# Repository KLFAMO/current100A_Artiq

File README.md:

# current100A_Artiq
100A current driver compatible with Artiq. At the moment, device is compatible with Sinara package size and includes all Sinara connectors. There is no software compatibility yet.

## High power circuit

Power supply - two wires (+ and -) from Delta Power Supply. (will be WAGO connector asap).
Warning: 

Coil 1 (L1) - two wires from one coil (will be WAGO connector asap)

Coil 2 (L2) - two wires from second coil (this coil is direction switchable) (will be WAGO connector asap)

LEM IN 100-S is used for current measurement.

## Control board

Power supply MSTBA green connector (0 and +12V) for control board.

Ethernet - User Interface communication.

SMA input - (-10V to +10V) current control by voltage (from external control program). 1V -> 10A

4x BNC inputs - not used yet

USB micro - not used yet

# User Interface

User interface is available via TCP/IP on port 10. Depending on configuration IP address is static or taken from DHCP - this must be set when programming uC. After connecting to the device user is able to change setting by sending commands.

## Commands
### Bbasic control

`MODE 0` - switch off current

`MODE 1` - current control via voltage input (SMA input on front panel)

`MODE 2` - current control via ethernet user interface (`CUR` command)

`CUR 10.2` - set current 10.2 A (only in mode 2)

`IMAX 25` - set max possible current value to 25A

`ERMAX 1` - max 1A change in each cycle (0.1ms)

### Advanced settings

`MODE 3` - set gate voltage using `VG` parameter

`I -0.04` - set gain -0.04 (this is bese gain for 50A - it is rescaled by uC for lower current due to udjust transistor characteristics)

`DIR x` - L2 coil current direction (x=-1: current positive, x=1: current negative, x=0: no current - all transistors blocked)

`DST x` - direction switching treshold; current direction switchin in coil L2 is possible only if absolute current value is less than x

`VG` - current gate voltage; in `MODE 3` is set manually

`CALIB 1` - gate voltage - current characteristics callibration. Improves current control.

`CALIB 4` - LEM zero current callibration (automaticaly done during startup)

## License

[MIT](https://opensource.org/licenses/MIT)

# Acknowledgments
This work has received funding from the European Partnership on Metrology, co-financed by the European Union’s Horizon Europe Research and Innovation Programme and by the Participating States, under grant number 22IEM01 TOCK.

# Issues

Please add your comments in `Issues` Github section (in top of this website).

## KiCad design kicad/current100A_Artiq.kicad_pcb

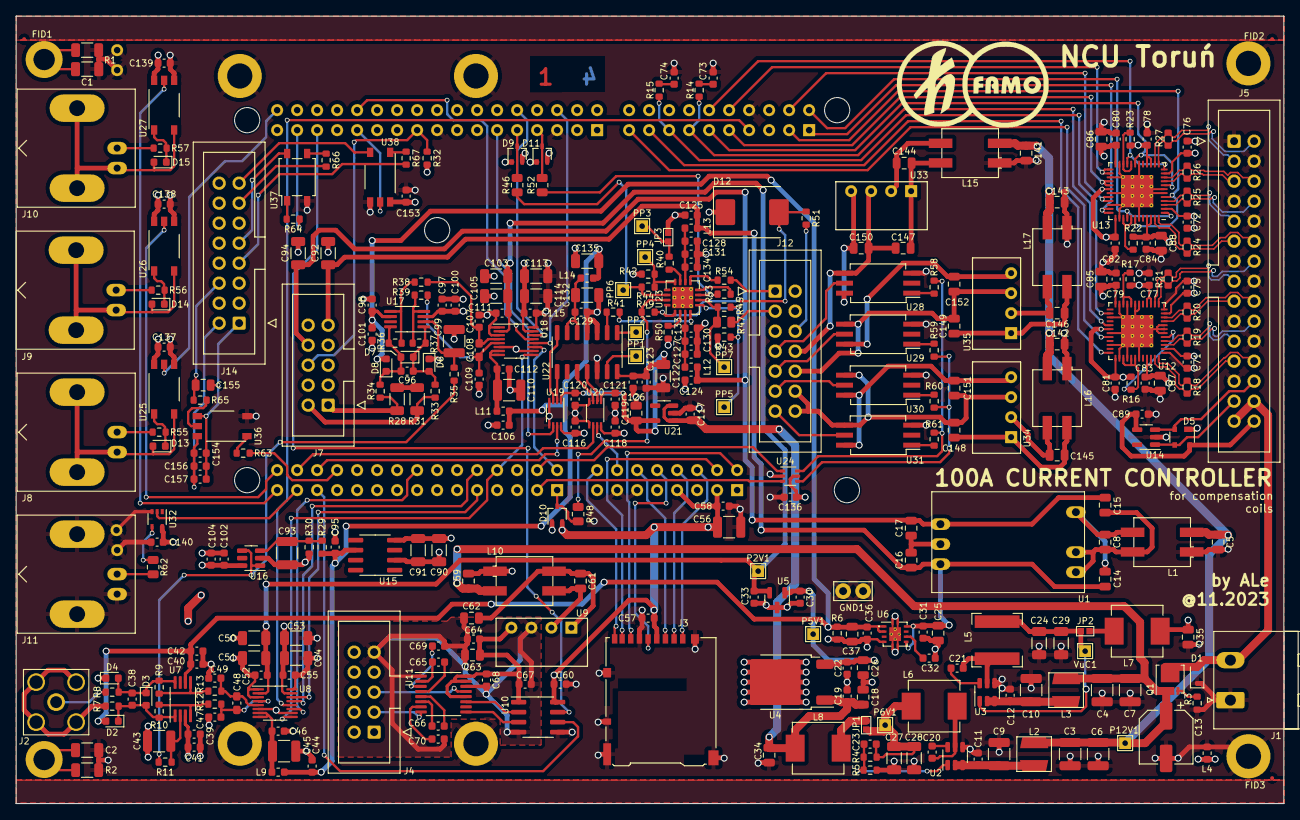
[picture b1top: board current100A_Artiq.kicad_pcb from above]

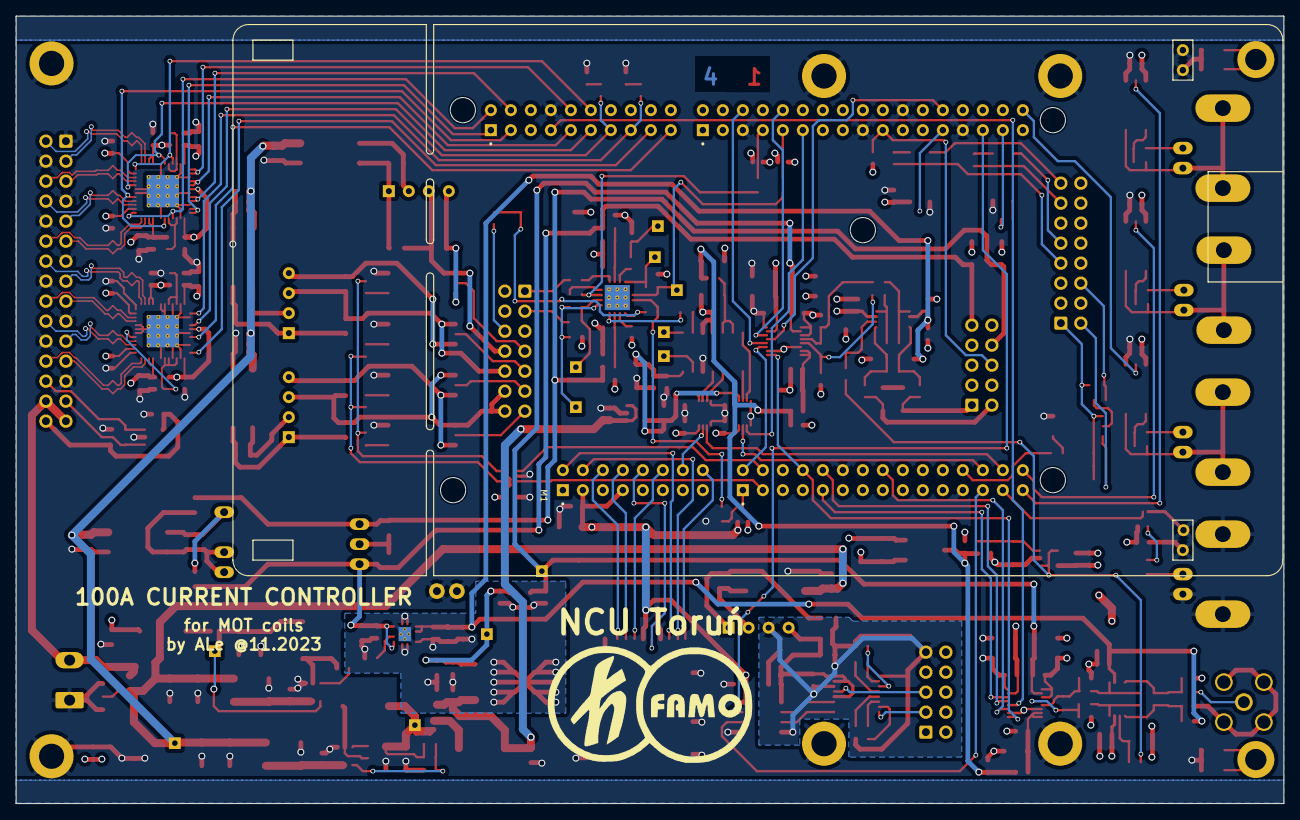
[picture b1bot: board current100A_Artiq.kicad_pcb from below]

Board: 4 copper layers, 161.0 x 100.0 mm, 337 parts (2 on the bottom side), 210 nets.

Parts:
C1, C2: GCJ31BR73A102KXJ1L; C_1206_3216Metric
C3, C4, C6, C7, C56: 10u X7R 50V; C_1210_3225Metric
C5, C8, C16, C17, C18, C25, C26, C37, C59, C61, C63, C141, C142, C143, C144, C145, C146, C150, C151, C152: GRM21BR61E106KA73L; C_0805_2012Metric
C9, C10: GCM32ER71E106KA57K; C_1210_3225Metric
C11, C12, C19, C20, C21, C22, C30, C31, C33, C36, C57, C58, C60, C64, C65, C67, C68, C71, C72, C75, C76, C77, C78, C79, C80, C81, C82, C83, C84, C89, C116, C118, C120, C121, C130, C131, C136, C137, C138, C139, C140, C153, C156: 100n 50V X7R; C_0603_1608Metric
C13: UCW1E470MCL1GS; CP_Elec_6.3x7.7
C14, C15, C62, C147, C148, C149: 1n C0G 100V; C_0805_2012Metric
C23, C39, C40, C46, C52, C55, C97, C98, C102, C111, C112, C126, C129, C133, C134, C154: 100p 50V C0G; C_0603_1608Metric
C24, C27, C28, C29: GRM31CR71A226KE15L; C_1206_3216Metric
C32: GRM1885C1H103JA01D; C_0603_1608Metric
C34, C35, C85, C86, C87, C88: GRM21BR71A106KA73L; C_0805_2012Metric
C38, C47, C49, C96, C107, C109: 1n 50V C0G; C_0603_1608Metric
C41, C42, C44, C95, C100, C101, C104, C106, C117, C124, C125, C127, C128, C157: GCM188R71E105KA64J; C_0603_1608Metric
C43, C93, C99: C1210C334J3JACAUTO; C_1210_3225Metric
C45, C110: 47UF 10V X7R; C_1210_3225Metric
C48, C108: 470p 50V C0G; C_0603_1608Metric_Pad1.08x0.95mm_HandSolder
C50, C53, C90, C92, C94, C103, C113, C122: GCM31CR71C106KA64L; C_1206_3216Metric
C51, C54, C91, C105, C114, C132, C135: GRM31C5C1H104JA01L; C_1206_3216Metric
C66, C69, C70: GCM188R71E474KA64D; C_0603_1608Metric
C73, C74: 82p 50V C0G; C_0603_1608Metric
C115: 100p C0G 50V; C_0603_1608Metric
C119: GCM21BR71C335KA73L; C_0805_2012Metric
C123: GRM31C5C1H104JA01L; C_0603_1608Metric
C155: 22n C0G 25V; C_0805_2012Metric
D1: SD12C-01FTG; D_SOD-323
D2, D4, D6, D8: TSS40U-RGG; D_0603_1608Metric
D3, D7: CZRU52C4V3; D_0603_1608Metric
D5: WE 8240136; SOT-143
D9, D10, D11: BAT54SW; SOT-323_SC-70
D12: 5.0SMDJ12AS; D_SMC
D13, D14, D15: TS4148C RZG; D_0603_1608Metric
FID1, FID2, FID3: Fiducial; Fiducial_0.5mm_Mask1.5mm
G1: KL_FAMO_LOGO; kl_famo_logo
G2: KL_FAMO_LOGO; kl_famo_logo_small
GND1: PAD; TestPoint_Bridge_Pitch2.54mm_Drill1.0mm
H1, H2: MountingHole_Pad; MountingHole_2.7mm_M2.5_DIN965_Pad
H3, H4, H5, H6, H7, H8: MountingHole_Pad; MountingHole_3.2mm_M3_DIN965_Pad
J1: MSTBA2.5/2-G-5.08 1757242; PhoenixContact_MSTBA_2,5_2-G-5,08_1x02_P5.08mm_Horizontal
J2: RF2-49B-T-00-50-G-HDW; SMA_Amphenol_132203-12_Horizontal
J3: DM3AT-SF-PEJM5; microSD_HC_Hirose_DM3AT-SF-PEJM5
J4, J7: N2510-6002-RB; IDC-Header_2x05_P2.54mm_Vertical
J5: N2530-6002-RB; IDC-Header_2x15_P2.54mm_Vertical
J8: B6252H5-NPP3G-50; BNC_Amphenol_B6252HB-NPP3G-50_Horizontal
J9, J10, J11: 5227161-1; BNC_Amphenol_B6252HB-NPP3G-50_Horizontal
J12: N2514-6002RB; IDC-Header_2x07_P2.54mm_Vertical
J14: N2516-6002-RB; IDC-Header_2x08_P2.54mm_Vertical
JP1, JP2: Jumper_NO_Small; GS2_small
JP3: Jumper_2_Bridged; GS2_small
L1, L10, L15, L16, L17: 50225C Murata; L_CommonMode_Murata_5000
L2, L3: LQH44PH220MPRL; L_MURATA_LQH44
L4: BLM18KG331SN1D; L_0603_1608Metric
L5: SRN6045-3R3Y; L_Bourns-SRN6028
L6: IHLP2525CZER100M01; L_Vishay_IHLP-2525
L7, L8: IHLP2525CZER220M11; L_Vishay_IHLP-2525
L9, L11, L12, L13, L14: BLM18HE102SN1D; L_0603_1608Metric
M1: NUCLEO-H743ZI; MODULE_NUCLEO-F746ZG_mini_M
P2V1, P5V1, P6V1, P12V1: TestPoint; TestPoint_THTPad_1.5x1.5mm_Drill0.7mm
PP1, PP2, PP3, PP4, PP5, PP6, PP7: PAD; TestPoint_THTPad_1.5x1.5mm_Drill0.7mm
Q1: SISS27DN-T1-GE3; Diodes_PowerDI3333-8
R1, R2: HV732BTTD1004F; R_1206_3216Metric
R3, R6, R44, R51, R65: 10k 1%; R_0603_1608Metric
R4, R5: 196k 1%; R_0603_1608Metric
R7, R8, R33, R34: 4,99k 1%; R_0603_1608Metric
R9, R10, R36, R37: 2k 1%; R_0603_1608Metric
R11, R32, R35, R40, R41, R43, R45, R49, R53, R54, R55, R56, R57, R63, R64, R67: 1k 1%; R_0603_1608Metric
R12, R13, R38, R39: 49,9R 1%; R_0603_1608Metric
R14, R15: 220R 1%; R_0603_1608Metric
R16, R17, R18, R19, R20, R21, R22, R23, R24, R25, R26, R27: 100R 1%; R_0603_1608Metric
R28, R31: RQ73C2B20RBTD; R_1206_3216Metric
R29, R30: 10k 0,1% 10ppm; R_0603_1608Metric
R42: DNP; R_0603_1608Metric
R46, R47, R48, R52: 100R 1%; R_0805_2012Metric
R50: 910R 1%; R_0603_1608Metric
R58, R59, R60, R61: 150R 1%; R_0603_1608Metric
R62: 100R; R_0805_2012Metric
R66: 2k4 1%; R_0603_1608Metric
U1: TME1215S; TDK_DCDC_CCG6_10
U2: AP63200WU-7; TSOT-23-6
U3: AP63203WU-7; TSOT-23-6
U4: LD29150DT50R; TO-252-2
U5: AP7313-25SAG-7; SOT-23
U6: TPS7A3001DRBx; Texas_VSON-8_1EP_3x3mm_P0,65mm_vias
U7, U17: THS4561IDGKx; MSOP-8_3x3mm_P0.65mm
U8, U18: LTC2380CMS-24#PBF; MSOP-16_3x4mm_P0.5mm
U9: AM1SS-1203SJZ; AM1SS-xxxxS
U10: ADuM121N; SOIC-8_3.9x4.9mm_P1.27mm
U11: MAX3221ExPWR; TSSOP-16_4.4x5mm_P0.65mm
U12, U13: SN65MLVD040RGZT; VQFN-48-1EP_7x7mm_P0.5mm_EP4.1x4.1mm_ThermalVias
U14: 24AA02E48T-I/OT; SOT-23-5
U15: ADR4540BRZ; SOIC-8_3.9x4.9mm_P1.27mm
U16: ADA4895-1ARJZ; SOT-23-6
U19, U20: 74LVC2T45DC,125; VSSOP-8_2.3x2mm_P0.5mm
U21: LP2981-50DBVR; SOT-23-5
U22: MAX5719AGSD+; SOIC-14_3.9x8.7mm_P1.27mm
U23: OPA4191xRUMx; WQFN-16-1EP_4x4mm_P0.65mm_EP2.7x2.7mm_ThermalVias
U24: NC7WZ17P6X; SOT-363_SC-70-6
U25, U26, U27, U36, U38: TLP2361(TPL,E; MFSOP6-5_4.4x3.6mm_P1.27mm
U28, U29, U30, U31: TLP701AF(F); SSO-6_6.8x4.6mm_P1.27mm_Clearance7mm
U32: NL17SZ16DFT2G; SOT-353_SC-70-5
U33, U34, U35: TME1215S; AM1SS-xxxxS
U37: TLP175A; SO-4_4.4x4.3mm_P2.54mm
VuC1: TestPoint; TestPoint_THTPad_1.5x1.5mm_Drill0.7mm

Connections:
+2V5: C33.2, C50.1, C51.2, C52.1, C103.1, C105.2, C111.1, P2V1.1, U5.2 (VO), U8.2 (VDD), U18.2 (VDD)
+3V3: C35.1, C53.1, C54.2, C55.1, C56.1, C57.1, C58.1, C60.2, C71.1, C72.1, C75.1, C76.1, C77.1, C78.1, C79.1, C80.1, C81.1, C82.1, C83.1, C84.1, C85.1, C86.1, C87.1, C88.1, C113.1, C114.2, C115.1, C116.2, C118.2, C136.1, C137.1, C138.1, C139.1, C140.1, C153.1, D9.2 (K), D10.2 (K), D11.2 (K), J3.4 (VDD), L7.1, M1.CN8_3 (IOREF_CN8), M1.CN8_7 (+3V3_CN8), R16.2, R17.2, R22.2, R23.2, R32.1, U8.15 (OVDD), U10.8 (VDD2), U12.2 (VCC), U12.11 (VCC), U12.15 (VCC), U12.16 (VCC), U12.24 (VCC), U12.30 (PDN), U12.37 (VCC), U12.45 (VCC), U12.46 (VCC), U13.2 (VCC), U13.11 (VCC), U13.15 (VCC), U13.16 (VCC), U13.24 (VCC), U13.30 (PDN), U13.37 (VCC), U13.45 (VCC), U13.46 (VCC), U18.15 (OVDD), U19.8 (VCCB), U20.8 (VCCB), U24.5 (V+), U25.6 (VCC), U26.6 (VCC), U27.6 (VCC), U32.5 (V+), U38.6 (VCC)
+4V: C44.1, C95.1, C106.1, C135.1, L9.1, L11.1, L14.1, R29.1, U15.6 (VOUT)
+5VA: C22.2, C26.1, C30.2, C39.1, C41.1, C90.1, C91.2, C97.1, C100.1, C102.1, C104.1, D4.1 (K), D6.1 (K), P5V1.1, U4.3 (OUT), U5.1 (VI), U7.3 (V+), U15.2 (VIN), U16.6 (V+), U17.3 (V+)
+5VD: C119.1, C120.2, C121.2, C122.1, C123.2, C126.1, U19.1 (VCCA), U20.1 (VCCA), U21.5 (VOUT), U22.14 (VDD)
+6V: C18.1, C19.2, C34.1, C117.1, L8.1, U4.1 (INP), U21.1 (VIN), U21.3 (ON/~OFF)
+12V: C3.1, C4.1, C5.1, C6.1, C7.1, C13.1, C59.1, C141.1, C142.1, C143.1, L1.2, L2.2, L3.2, L10.2, L15.2, L16.2, L17.2, P12V1.1, Q1.1 (S), Q1.2 (S), Q1.3 (S)
+15V: C15.1, C17.2, C94.1, C124.1, J7.8, L12.2, U1.4 (+VOUT)
-15V: C14.1, C16.1, C25.1, C31.1, C92.1, C125.1, J7.9, L13.2, U1.6 (-VOUT), U6.5 (EN), U6.8 (IN)
-VSW: C36.1, C37.1, C40.2, C42.2, C98.2, C101.2, D2.2 (A), D8.2 (A), R6.1, U6.1 (OUT), U6.2 (FB), U7.6 (V-), U17.6 (V-)
/15A_ON: M1.CN9_30 (D64/PG1/IO), U26.5 (VO)
/100A_ON: M1.CN9_29 (D65/PG0/IO), U27.5 (VO)
/ADC_CNV: M1.CN9_8 (D54/PD4/USART_B_RTS), U8.9 (CNV), U18.9 (CNV)
/AUX_SPAN: D9.3 (COM), M1.CN10_9 (A7/PF5/ADC3_IN4), R46.2
/Analog input1/ADC1INM: R9.2, R13.2, U7.5 (-)
/Analog input1/ADC1INP: R10.2, R12.2, U7.4 (+)
/Analog input1/IN_gnd: J2.2 (Ext), R7.1
/Analog input1/VREFB: C45.1, C46.1, L9.2, U8.7 (REF), U8.8 (REF/*DGC)
/Analog input1/VREF_P: R11.2, R35.2, U16.1, U16.4 (-)
/COIL_SPAN: D10.3 (COM), M1.CN9_1 (A0/PA3/ADC123_IN3), R48.2
/DEL_CC: M1.CN10_25 (D31/PE2/QSPI_BK1_IO2), U38.5 (VO)
/DEL_PWM: M1.CN9_24 (D61/PF8/SAI_B_SCK), R63.2
/DEL_RSD: M1.CN10_31 (XD33/PB0/TIMER_D_PWM1), R64.2
/DIR_L2: M1.CN10_34 (D35/PB11/TIMER_C_PWM3), U25.5 (VO)
/Digital inputs/output1/12V_pom4: C144.1, L15.3, U33.2 (+VIN)
/Digital inputs/output1/12V_pom5: C145.1, L16.3, U34.2 (+VIN)
/Digital inputs/output1/12V_pom6: C146.1, L17.3, U35.2 (+VIN)
/Digital inputs/output1/GT1: J12.7, U28.5 (VO)
/Digital inputs/output1/GT2: J12.9, U29.5 (VO)
/Digital inputs/output1/GT3: J12.11, U30.5 (VO)
/Digital inputs/output1/GT4: J12.13, U31.5 (VO)
/Digital inputs/output1/L2_LEFTB: R58.2, R61.2, U24.6
/Digital inputs/output1/L2_RIGHTB: R59.2, R60.2, U24.4
/Digital inputs/output1/ST1: C147.1, C150.2, J12.8, U28.4 (VEE), U33.3 (-VOUT)
/Digital inputs/output1/ST2: C149.1, C152.2, J12.10, U29.4 (VEE), U35.3 (-VOUT)
/Digital inputs/output1/ST3: C148.1, C151.2, J12.12, J12.14, U30.4 (VEE), U31.4 (VEE), U34.3 (-VOUT)
/Digital inputs/output1/VT1: C150.1, U28.6 (VCC), U33.4 (+VOUT)
/Digital inputs/output1/VT2: C152.1, U29.6 (VCC), U35.4 (+VOUT)
/Digital inputs/output1/VT3: C151.1, U30.6 (VCC), U31.6 (VCC), U34.4 (+VOUT)
/Digital inputs/output1/gnd_pom4: C144.2, C147.2, L15.4, U33.1 (-VIN)
/Digital inputs/output1/gnd_pom5: C145.2, C148.2, L16.4, U34.1 (-VIN)
/Digital inputs/output1/gnd_pom6: C146.2, C149.2, L17.4, U35.1 (-VIN)
/Kasli interface/I2C_SCL: D5.3 (I/O2), J5.27, U14.1 (SCL)
/Kasli interface/I2C_SDA: D5.2 (I/O1), J5.26, U14.3 (SDA)
/Kasli interface/LVDS0_N: J5.3, R27.1, U13.14 (4B)
/Kasli interface/LVDS0_P: J5.2, R27.2, U13.13 (4A)
/Kasli interface/LVDS1_N: J5.6, R26.1, U13.10 (3B)
/Kasli interface/LVDS1_P: J5.5, R26.2, U13.9 (3A)
/Kasli interface/LVDS2_N: J5.9, R25.1, U13.4 (2B)
/Kasli interface/LVDS2_P: J5.8, R25.2, U13.3 (2A)
/Kasli interface/LVDS3_N: J5.12, R24.1, U13.48 (1B)
/Kasli interface/LVDS3_P: J5.11, R24.2, U13.47 (1A)
/Kasli interface/LVDS4_N: J5.15, R21.1, U12.14 (4B)
/Kasli interface/LVDS4_P: J5.14, R21.2, U12.13 (4A)
/Kasli interface/LVDS5_N: J5.18, R20.1, U12.10 (3B)
/Kasli interface/LVDS5_P: J5.17, R20.2, U12.9 (3A)
/Kasli interface/LVDS6_N: J5.21, R19.1, U12.4 (2B)
/Kasli interface/LVDS6_P: J5.20, R19.2, U12.3 (2A)
/Kasli interface/LVDS7_N: J5.24, R18.1, U12.48 (1B)
/Kasli interface/LVDS7_P: J5.23, R18.2, U12.47 (1A)
/Kasli interface/P3V3_MP: C89.1, D5.4 (VCC), J5.30, U14.4 (V_{CC})
/L2_LEFT: M1.CN9_4 (D52/PD6/USART_B_RX), U24.1
/L2_RIGHT: M1.CN9_3 (A1/PC0/ADC123_IN10), U24.3
/LEM_ADC: M1.CN10_10 (D3/PE13/TIMER_A_PWM3), U18.14 (SDO)
/LEM_BUSY: M1.CN9_2 (D51/PD7/USART_B_SCLK), U18.11 (BUSY)
/LEM_OK: J7.6, M1.CN10_19 (D28/PD13/QSPI_BK1_IO3), R32.2
/LEM_RDL: M1.CN10_6 (D5/PE11/TIMER_A_PWM2), U18.12 (RDL/SDI)
/LEM_SCK: M1.CN10_26 (D39/PE12/TIMER_A_PWM3N), U18.13 (SCK)
/MOS_CLK: M1.CN9_26 (D62/PF7/SAI_B_MCLK), U19.7 (1B)
/MOS_CS: M1.CN10_11 (A8/PF6/ADC3_IN8), U19.6 (2B)
/MOS_DATA: M1.CN9_28 (D63/PF9/SAI_B_FS), U20.6 (2B)
/MOS_LDAC: M1.CN8_14 (D49/PG2/IO), U20.7 (1B)
/Main Current sensor1/ADC1INM: R37.2, R39.2, U17.4 (+)
/Main Current sensor1/ADC1INP: R36.2, R38.2, U17.5 (-)
/Main Current sensor1/LEM_c: R28.2, R31.1
/Main Current sensor1/LEM_out1: J7.1, R28.1, R34.1
/Main Current sensor1/LEM_out2: J7.2, R31.2, R33.1
/Main Current sensor1/VREFA: C110.1, C112.1, L11.2, U18.7 (REF), U18.8 (REF/*DGC)
/Nucleo-H743ZI1/SCPI_RX: M1.CN9_25 (D67/PD0/CAN_RX), U10.6 (VOB)
/Nucleo-H743ZI1/SCPI_TX: M1.CN10_29 (D32/PA0/TIMER_C_PWM1), U10.7 (VIA)
/Nucleo-H743ZI1/SCPI_interface/12V_pom3: C61.1, L10.3, U9.2 (+VIN)
/Nucleo-H743ZI1/SCPI_interface/VDISO: C63.1, C64.2, C67.2, C68.2, U9.4 (+VOUT), U10.1 (VDD1), U11.12 (FORCEON), U11.15 (VCC), U11.16 (~FORCEOFF)
/Nucleo-H743ZI1/SCPI_interface/VSISO: C62.1, C63.2, C64.1, C67.1, C68.1, C69.1, C70.1, J4.9, U9.3 (-VOUT), U10.4 (GND1), U11.1 (~EN), U11.14 (GND)
/Nucleo-H743ZI1/SCPI_interface/gnd_pom3: C61.2, C62.2, L10.4, U9.1 (-VIN)
/Nucleo-H743ZI1/SD_CK: J3.5 (CLK), M1.CN8_10 (D47/PC12/SDMMC_CK)
/Nucleo-H743ZI1/SD_CMD: J3.3 (CMD), M1.CN8_12 (D48/PD2/SDMMC_CMD)
/Nucleo-H743ZI1/SD_D0: J3.7 (DAT0), M1.CN8_2 (D43/PC8/SDMMC_D0)
/Nucleo-H743ZI1/SD_D1: J3.8 (DAT1), M1.CN8_4 (D44/PC9/SDMMC_D1/I2S_A_CKIN)
/Nucleo-H743ZI1/SD_D2: J3.1 (DAT2), M1.CN8_6 (D45/PC10/SDMMC_D2)
/Nucleo-H743ZI1/SD_D3: J3.2 (DAT3/CD), M1.CN8_8 (D46/PC11/SDMMC_D3)
/Nucleo-H743ZI1/SD_DET: J3.9 (DET_B), M1.CN8_16 (D50/PG3/IO)
/Power grid generation1/3V_out: JP2.1, L7.2
/Power grid generation1/6V_out: JP1.1, L8.2
/Power grid generation1/12V_pom: C10.1, C12.1, L3.1, U3.2 (EN), U3.3 (IN)
/Power grid generation1/12V_pom1: C9.1, C11.1, L2.1, U2.2 (EN), U2.3 (IN)
/Power grid generation1/12V_pom2: C8.1, C14.2, L1.3, U1.3 (+VIN)
/Power grid generation1/gnd_pom: C8.2, C15.2, L1.4, U1.1 (-VIN), U1.2 (RC)
/Power grid generation1/sw_out: C24.1, C29.1, JP2.2, L5.1, U3.1 (FB), VuC1.1
/Power grid generation1/sw_out1: C23.1, C27.1, C28.1, JP1.2, L6.1, P6V1.1, R4.1
/Power grid generation1/switch: C21.1, L5.2, U3.5 (SW)
/Power grid generation1/switch1: C20.1, L6.2, U2.5 (SW)
/SET_ADC: M1.CN9_9 (A4/PC2(PB9)/ADC3_IN12/I2C1_SDA), U8.14 (SDO)
/SET_BUSY: M1.CN9_16 (D57/PE4/SAI_A_FS), U8.11 (BUSY)
/SET_RDL: M1.CN7_7 (D19/PB12/I2S_A_WS), U8.12 (RDL/SDI)
/SET_SCK: M1.CN9_10 (D55/PD3/USART_B_CTS), U8.13 (SCK)
/T0_SPAN: D11.3 (COM), M1.CN10_7 (A6/PF4/ADC3_IN9), R52.2
/TO_C15A: M1.CN9_27 (D66/PD1/CAN_TX), U32.2
DAT4: M1.CN7_10 (D13/PA5/SPI_A_SCK), U13.25 (4D), U13.26 (4R)
DAT4_OUT: M1.CN7_12 (D12/PA6/SPI_A_MISO), U13.12 (4DE), U13.21 (~4RE)
DAT5: M1.CN7_9 (XD20/PA15/I2S_B_WS), U13.28 (3D), U13.29 (3R)
DAT5_OUT: M1.CN7_11 (D21/PC7/I2S_B_MCK), U13.8 (3DE), U13.19 (~3RE)
DAT6: M1.CN7_4 (D14/PB9/I2C_A_SDA), U13.32 (2D), U13.33 (2R)
DAT6_OUT: M1.CN7_3 (D17/PB15/I2S_A_SD), U13.5 (2DE), U13.42 (~2RE)
DAT7: M1.CN7_1 (D16/PC6/I2S_A_MCK), U13.35 (1D), U13.36 (1R)
DAT7_OUT: M1.CN7_2 (D15/PB8/I2C_A_SCL), U13.1 (1DE), U13.40 (~1RE)
DT0: J12.1, R54.2
GND: C1.2, C2.2, C3.2, C4.2, C5.2, C6.2, C7.2, C9.2, C10.2, C11.2, C12.2, C13.2, C24.2, C27.2, C28.2, C29.2, C34.2, C35.2, C53.2, C54.1, C55.2, C56.2, C57.2, C58.2, C59.2, C60.1, C71.2, C72.2, C73.2, C74.2, C75.2, C76.2, C77.2, C78.2, C79.2, C80.2, C81.2, C82.2, C83.2, C84.2, C85.2, C86.2, C87.2, C88.2, C89.2, C113.2, C114.1, C115.2, C116.1, C117.2, C118.1, C119.2, C120.1, C121.1, C122.2, C123.1, C126.2, C136.2, C137.2, C138.2, C139.2, C140.2, C141.2, C142.2, C143.2, C153.2, D1.1 (A1), D5.1 (GND), GND1.1, H3.1, H4.1, H5.1, H6.1, H7.1, H8.1, J1.1, J3.6 (VSS), J3.10 (DET_A), J3.11 (SHIELD), J5.1, J5.4, J5.7, J5.10, J5.13, J5.16, J5.19, J5.22, J5.25, J11.2 (Ext), L1.1, L4.1, L10.1, L15.1, L16.1, L17.1, M1.35 (EXT_GND), M1.CN7_8 (GND_CN7), M1.CN8_11 (GND_CN8), M1.CN8_13 (GND_CN8), M1.CN9_12 (GND_CN9), M1.CN9_23 (GND_CN9), M1.CN10_5 (GND_CN10), M1.CN10_17 (GND_CN10), M1.CN10_22 (GND_CN10), M1.CN10_27 (GND_CN10), R1.2, R2.2, R3.2, R5.2, U2.4 (GND), U3.4 (GND), U8.16 (GND), U10.5 (GND2), U12.1 (1DE), U12.6 (GND), U12.7 (GND), U12.8 (3DE), U12.12 (4DE), U12.18 (GND), U12.19 (~3RE), U12.21 (~4RE), U12.23 (GND), U12.27 (GND), U12.31 (GND), U12.34 (GND), U12.38 (GND), U12.40 (~1RE), U12.43 (GND), U12.49 (EP), U13.6 (GND), U13.7 (GND), U13.18 (GND), U13.23 (GND), U13.27 (GND), U13.31 (GND), U13.34 (GND), U13.38 (GND), U13.43 (GND), U13.49 (EP), U14.2 (V_{SS}), U18.16 (GND), U19.4 (GND), U19.5 (DIR), U20.4 (GND), U20.5 (DIR), U21.2 (GND), U22.12 (DGND), U24.2 (V-), U25.4 (VEE), U26.4 (VEE), U27.4 (VEE), U28.3 (C), U29.3 (C), U30.3 (C), U31.3 (C), U32.3 (V-), U36.3 (C), U37.2, U38.4 (VEE)
GNDA: C16.2, C17.1, C18.2, C19.1, C22.1, C25.2, C26.2, C30.1, C31.2, C32.2, C33.1, C36.2, C37.2, C39.2, C40.1, C41.2, C42.1, C43.2, C44.2, C45.2, C46.2, C47.1, C49.2, C50.2, C51.1, C52.2, C90.2, C91.1, C92.2, C93.2, C94.2, C95.2, C97.2, C98.1, C99.2, C100.2, C101.1, C102.2, C103.2, C104.2, C105.1, C106.2, C107.1, C109.2, C110.2, C111.2, C112.2, C124.2, C125.2, C127.2, C128.1, C129.1, C130.1, C131.2, C132.2, C133.2, C134.1, C135.2, D9.1 (A), D10.1 (A), D11.1 (A), D12.1 (A1), J7.5, J7.7, J12.2, J12.4, JP3.1 (A), L4.2, M1.CN10_3 (AGND_CN10), R6.2, R30.2, R42.2, R43.2, R50.1, U1.5 (COM), U4.2 (GND), U5.3 (GND), U6.4 (GND), U6.9 (EP_1), U8.1 (CHAIN), U8.3 (GND), U8.6 (GND), U8.10 (GND), U15.4 (GND), U16.2 (V-), U18.1 (CHAIN), U18.3 (GND), U18.6 (GND), U18.10 (GND), U22.3 (AGNDF), U22.4 (AGNDS)
GT0: J12.3, R47.1
unnamed: C1.1, H1.1, R1.1
unnamed: C2.1, H2.1, R2.1
unnamed: C73.1, R14.2
unnamed: C74.1, R15.2
unnamed: C38.2, D2.1 (K), D3.2 (A), R7.2, R10.1, U7.1 (-)
unnamed: C38.1, D3.1 (K), D4.2 (A), R8.2, R9.1, U7.8 (+)
unnamed: C96.2, D6.2 (A), D7.1 (K), R33.2, R37.1, U17.1 (-)
unnamed: C96.1, D7.2 (A), D8.1 (K), R34.2, R36.1, U17.8 (+)
unnamed: D12.2 (A2), R49.2, R51.1, U23.1 (-)
unnamed: D13.2 (A), J8.2 (Ext), U25.3 (C)
unnamed: D13.1 (K), R55.2, U25.1 (A)
unnamed: D14.2 (A), J9.2 (Ext), U26.3 (C)
unnamed: D14.1 (K), R56.2, U26.1 (A)
unnamed: D15.2 (A), J10.2 (Ext), U27.3 (C)
unnamed: D15.1 (K), R57.2, U27.1 (A)
unnamed: J2.1 (In), R8.1
unnamed: J4.3, U11.8 (RIN)
unnamed: J4.5, U11.13 (DOUT)
unnamed: J8.1 (In), R55.1
unnamed: J9.1 (In), R56.1
unnamed: J10.1 (In), R57.1
unnamed: J11.1 (In), R62.1
unnamed: C154.2, C155.1, C156.2, C157.2, J14.1, U36.4 (VEE)
unnamed: C154.1, C156.1, C157.1, J14.2, U36.6 (VCC)
unnamed: C155.2, J14.6, R65.1
unnamed: J14.7, R67.1
unnamed: J14.9, U37.4
unnamed: J14.13, R66.1
unnamed: J14.15, U38.3 (C)
unnamed: JP3.2 (B), PP3.1, R40.2
unnamed: PP6.1, R44.1, R46.1, U23.14
unnamed: PP7.1, R45.1, R47.2, U23.6
unnamed: Q1.4 (G), R3.1
unnamed: R48.1, R49.1, U23.15
unnamed: R52.1, R53.1, U23.7
unnamed: R62.2, U32.4
unnamed: R64.1, U37.1
unnamed: R66.2, U37.3
unnamed: C20.2, U2.6 (BST)
unnamed: C23.2, R4.2, R5.1, U2.1 (FB)
unnamed: C21.2, U3.6 (BST)
unnamed: C32.1, U6.6 (NR/SS)
unnamed: C43.1, R11.1, U7.2 (VOCM)
unnamed: C47.2, C48.1, R12.1, U8.4 (IN+)
unnamed: C48.2, C49.1, R13.1, U8.5 (IN-)
unnamed: U10.3 (VIB), U11.9 (ROUT)
unnamed: U10.2 (VOA), U11.11 (DIN)
unnamed: C65.2, U11.2 (C1+)
unnamed: C65.1, U11.4 (C1-)
unnamed: C66.2, U11.5 (C2+)
unnamed: C66.1, U11.6 (C2-)
unnamed: C69.2, U11.3 (V+)
unnamed: C70.2, U11.7 (V-)
unnamed: R16.1, U12.5 (2DE), U12.39 (1FSEN), U12.41 (2FSEN), U12.42 (~2RE)
unnamed: R17.1, U12.20 (3FSEN), U12.22 (4FSEN)
unnamed: R22.1, U13.39 (1FSEN), U13.41 (2FSEN)
unnamed: R23.1, U13.20 (3FSEN), U13.22 (4FSEN)
unnamed: C93.1, R29.2, R30.1, U16.3 (+)
unnamed: C99.1, R35.1, U17.2 (VOCM)
unnamed: C107.2, C108.1, R38.1, U18.4 (IN+)
unnamed: C108.2, C109.1, R39.1, U18.5 (IN-)
unnamed: U19.2 (1A), U22.8 (SCLK)
unnamed: U19.3 (2A), U22.7 (~CS)
unnamed: U20.2 (1A), U22.11 (~LDAC)
unnamed: U20.3 (2A), U22.10 (DIN)
unnamed: PP1.1, U22.13 (INV)
unnamed: R41.2, U22.2 (OUT)
unnamed: C129.2, C132.1, L14.2, U22.5 (REFS), U22.6 (REFF)
unnamed: PP2.1, U22.1 (RFB)
unnamed: R50.2, U23.2 (+)
unnamed: R41.1, U23.4 (+)
unnamed: PP5.1, R43.1, R45.2, U23.5 (-)
unnamed: R54.1, U23.9 (+)
unnamed: R53.2, U23.8 (-)
unnamed: R40.1, U23.11 (+)
unnamed: PP4.1, R42.1, R44.2, U23.12 (-)
unnamed: C127.1, C130.2, C133.1, L12.1, U23.3 (V+)
unnamed: C128.2, C131.1, C134.2, L13.1, U23.10 (V-)
unnamed: R58.1, U28.1 (A)
unnamed: R59.1, U29.1 (A)
unnamed: R60.1, U30.1 (A)
unnamed: R61.1, U31.1 (A)
unnamed: R63.1, U36.1 (A)
unnamed: R65.2, U36.5 (VO)
unnamed: R67.2, U38.1 (A)
P12V0: D1.2 (A2), J1.2, J5.28, J5.29, Q1.5 (D)
SPI_MISO: M1.CN7_19 (D25/PB4/SPI_B_MISO), U12.32 (2D)
SPI_MOSI: M1.CN7_13 (D22/PB5/I2S_B_SD/SPI_B_MOSI), R14.1, U12.29 (3R)
SPI_NSS: M1.CN7_17 (D24/PA4/SPI_B_NSS), U12.36 (1R)
SPI_SCK: M1.CN7_15 (D23/PB3/I2S_B_CK/SPI_B_SCK), R15.1, U12.26 (4R)
ST34: J12.6, R51.2

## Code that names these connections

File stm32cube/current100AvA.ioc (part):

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Mcu.Name=STM32H743ZITx
Mcu.Package=LQFP144
Mcu.UserName=STM32H743ZITx
PA0.GPIOParameters=GPIO_Label
PA0.GPIO_Label=SCPI_TX
PA0.Mode=Asynchronous
PA0.Signal=UART4_TX
PA1.Mode=RMII
PA1.Signal=ETH_REF_CLK
PA11.Mode=Device_Only
PA11.Signal=USB_OTG_FS_DM
PA12.Mode=Device_Only
PA12.Signal=USB_OTG_FS_DP
PA15\ (JTDI).GPIOParameters=GPIO_Label
PA15\ (JTDI).GPIO_Label=DAT5
PA15\ (JTDI).Signal=GPXTI15
PA2.Mode=RMII
PA2.Signal=ETH_MDIO
PA3.GPIOParameters=GPIO_Label
PA3.GPIO_Label=COIL_SPAN
PA3.Signal=ADCx_INP15
PA4.GPIOParameters=GPIO_Label
PA4.GPIO_Label=SPI_NSS
PA4.Mode=NSS_Signal_Hard_Input
PA4.Signal=SPI1_NSS
PA5.GPIOParameters=GPIO_Label
PA5.GPIO_Label=DAT4
PA5.Signal=GPXTI5
PA6.GPIOParameters=GPIO_Label
PA6.GPIO_Label=DAT4_OUT
PA6.Signal=GPIO_Output
PA7.Mode=RMII
PA7.Signal=ETH_CRS_DV
PA8.Mode=Activate_SOF_FS
PA8.Signal=USB_OTG_FS_SOF
PA9.Mode=Activate_VBUS
PA9.Signal=USB_OTG_FS_VBUS
PB0.GPIOParameters=GPIO_Label
PB0.GPIO_Label=LD1 [Green Led]
PB0.Signal=GPIO_Output
PB11.GPIOParameters=GPIO_Label
PB11.GPIO_Label=DIR_L2
PB11.Signal=GPXTI11
PB12.GPIOParameters=GPIO_Label
PB12.GPIO_Label=SET_RDL
PB12.Signal=GPIO_Output
PB13.Mode=RMII
PB13.Signal=ETH_TXD1
PB14.GPIOParameters=GPIO_Label
PB14.GPIO_Label=LD3 [Red Led]
PB14.Signal=GPIO_Output
PB15.GPIOParameters=GPIO_Label
PB15.GPIO_Label=DAT6_OUT
PB15.Signal=GPIO_Output
PB3\ (JTDO/TRACESWO).GPIOParameters=GPIO_Label
PB3\ (JTDO/TRACESWO).GPIO_Label=SPI_SCK
PB3\ (JTDO/TRACESWO).Mode=Full_Duplex_Slave
PB3\ (JTDO/TRACESWO).Signal=SPI1_SCK
PB4\ (NJTRST).GPIOParameters=GPIO_Label
PB4\ (NJTRST).GPIO_Label=SPI_MISO
PB4\ (NJTRST).Mode=Full_Duplex_Slave
PB4\ (NJTRST).Signal=SPI1_MISO
PB5.GPIOParameters=GPIO_Label
PB5.GPIO_Label=SPI_MOSI
PB5.Mode=Full_Duplex_Slave
PB5.Signal=SPI1_MOSI
PB6.GPIOParameters=GPIO_Label
PB6.GPIO_Label=EEP_SCL
PB6.Mode=I2C
PB6.Signal=I2C1_SCL
PB7.GPIOParameters=GPIO_Label
PB7.GPIO_Label=EEP_SDA
PB7.Mode=I2C
PB7.Signal=I2C1_SDA
PB8.GPIOParameters=GPIO_Label
PB8.GPIO_Label=DAT7_OUT
PB8.Signal=GPIO_Output
PB9.GPIOParameters=GPIO_Label
PB9.GPIO_Label=DAT6
PB9.Signal=GPXTI9
PC0.GPIOParameters=GPIO_Label
PC0.GPIO_Label=L2_RIGHT
PC0.Signal=GPIO_Output
PC1.Mode=RMII
PC1.Signal=ETH_MDC
PC13.GPIOParameters=GPIO_Label
PC13.GPIO_Label=B1 [Blue PushButton]
PC13.Signal=GPIO_Input
PC14-OSC32_IN\ (OSC32_IN).Signal=RCC_OSC32_IN
PC15-OSC32_OUT\ (OSC32_OUT).Signal=RCC_OSC32_OUT
PC2_C.GPIOParameters=GPIO_Label
PC2_C.GPIO_Label=SET_ADC
PC2_C.Mode=Full_Duplex_Master
PC2_C.Signal=SPI2_MISO
PC3_C.Mode=Full_Duplex_Master
PC3_C.Signal=SPI2_MOSI
PC4.Mode=RMII
PC4.Signal=ETH_RXD0
PC5.Mode=RMII
PC5.Signal=ETH_RXD1
PC6.GPIOParameters=GPIO_Label
PC6.GPIO_Label=DAT7
PC6.Signal=GPXTI6
PC7.GPIOParameters=GPIO_Label
PC7.GPIO_Label=DAT5_OUT
PC7.Signal=GPIO_Output
PD0.GPIOParameters=GPIO_Label
PD0.GPIO_Label=SCPI_RX
PD0.Mode=Asynchronous
PD0.Signal=UART4_RX
PD10.GPIOParameters=GPIO_Label
PD10.GPIO_Label=USB_OTG_FS_PWR_EN
PD10.Signal=GPIO_Output
PD13.GPIOParameters=GPIO_Label
PD13.GPIO_Label=LEM_OK
PD13.Signal=GPXTI13
PD3.GPIOParameters=GPIO_Label
PD3.GPIO_Label=SET_SCK
PD3.Mode=Full_Duplex_Master
PD3.Signal=SPI2_SCK
PD4.GPIOParameters=GPIO_Label
PD4.GPIO_Label=ADC_CNV
PD4.Signal=GPIO_Output
PD6.GPIOParameters=GPIO_Label
PD6.GPIO_Label=L2_LEFT
PD6.Signal=GPIO_Output
PD7.GPIOParameters=GPIO_Label
PD7.GPIO_Label=LEM_BUSY
PD7.Signal=GPXTI7
PD8.GPIOParameters=GPIO_Label
PD8.GPIO_Label=STLINK_RX
PD8.Mode=Asynchronous
PD8.Signal=USART3_TX
PD9.GPIOParameters=GPIO_Label
PD9.GPIO_Label=STLINK_TX
PD9.Mode=Asynchronous
PD9.Signal=USART3_RX
PE1.GPIOParameters=GPIO_Label
PE1.GPIO_Label=LD2 [Yellow Led]
PE1.Signal=GPIO_Output
PE11.GPIOParameters=GPIO_Label
PE11.GPIO_Label=LEM_RDL
PE11.Signal=GPIO_Output
PE12.GPIOParameters=GPIO_Label
PE12.GPIO_Label=LEM_SCK
PE12.Mode=Full_Duplex_Master
PE12.Signal=SPI4_SCK
PE13.GPIOParameters=GPIO_Label
PE13.GPIO_Label=LEM_ADC
PE13.Mode=Full_Duplex_Master
PE13.Signal=SPI4_MISO
PE2.GPIOParameters=GPIO_Label
PE2.GPIO_Label=DEL_CC
PE2.Signal=GPXTI2
PE4.GPIOParameters=GPIO_Label
PE4.GPIO_Label=SET_BUSY
PE4.Signal=GPXTI4
PE6.Mode=Full_Duplex_Master
PE6.Signal=SPI4_MOSI
PF4.GPIOParameters=GPIO_Label
PF4.GPIO_Label=T0_SPAN
PF4.Mode=IN9-Single-Ended
PF4.Signal=ADC3_INP9
PF5.GPIOParameters=GPIO_Label
PF5.GPIO_Label=AUX_SPAN
PF5.Mode=IN4-Single-Ended
PF5.Signal=ADC3_INP4
PF6.GPIOParameters=GPIO_Label
PF6.GPIO_Label=MOS_CS
PF6.Signal=GPIO_Output
PF7.GPIOParameters=GPIO_Label
PF7.GPIO_Label=MOS_CLK
PF7.Mode=TX_Only_Simplex_Unidirect_Master
PF7.Signal=SPI5_SCK
PF8.GPIOParameters=GPIO_Label
PF8.GPIO_Label=DEL_PWM
PF8.Signal=S_TIM13_CH1
PF9.GPIOParameters=GPIO_Label
PF9.GPIO_Label=MOS_DATA
PF9.Mode=TX_Only_Simplex_Unidirect_Master
PF9.Signal=SPI5_MOSI
PG0.GPIOParameters=GPIO_Label
PG0.GPIO_Label=_100A_ON
PG0.Signal=GPXTI0
PG1.GPIOParameters=GPIO_Label
PG1.GPIO_Label=_15A_ON
PG1.Signal=GPXTI1
PG11.Mode=RMII
PG11.Signal=ETH_TX_EN
PG13.Mode=RMII
PG13.Signal=ETH_TXD0
PG2.GPIOParameters=GPIO_Label
PG2.GPIO_Label=MOS_LDAC
PG2.Signal=GPIO_Output
PG3.GPIOParameters=GPIO_Label
PG3.GPIO_Label=SD_DET
PG3.Signal=GPXTI3
PH0-OSC_IN\ (PH0).Signal=RCC_OSC_IN
PH1-OSC_OUT\ (PH1).Signal=RCC_OSC_OUT
RCC.HSE_VALUE=8000000
RCC.SYSCLKFreq_VALUE=64000000
board=NUCLEO-H743ZI2
boardIOC=true

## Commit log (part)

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2024-08-12 adding kicad project made by ALe
2024-08-12 created stm32cube project based on ioc file from kicad
2024-08-13 added rtos, tests on uart3 and ld1 blink in separate tasks
2024-09-04 not working yet
2024-09-08 works on adc, initially works for adc-set, but need to be tested
2024-09-10 dac initially works, need some optimisation
2024-09-10 adc lem and set initial calibration
2024-09-12 first simple pid only with I
2024-09-13 adding eth and lwip, but not ready yet
2024-09-22 changed name of stm project to _old
2024-09-23 importing copy of nucleo-eth-template
2024-09-23 remove stm32cube because of problem with git submodule
2024-09-23 added stm32cube without .git
2024-09-25 copy ethernet_test - without rtos, initial eth tests work
2024-09-25 adding spi2 - adc-set, (eth works)
2024-09-25 adding spi4-lem-adc, changed device name in eth console
2024-09-25 added input signals for adcs
2024-09-25 adding spi5-mos-dac and some variables
2024-09-25 setting tim7 to around 1s period, and test-works
2024-09-26 adcs works, but not well calibrated
2024-09-26 DAC works but not callibrated
2024-09-26 initially working stabilisation v_set -> v_lem
2024-09-27 controller times optimisation
2024-09-30 adding I to menu, pid cycle = 500us
2024-10-04 adding mode parameter and bridge transistors gate control
2024-10-09 adding some limits to controller, changing average to 100 and cycle to 300us
2024-10-22 Preparing for testing in Sr4 experiment
2024-10-23 notes
2024-10-23 readme and adding rI parameter
2024-10-23 image - front panel
2024-10-23 Adding images to readme
2024-11-28 setting server ip from gnetif, switching to dhcp mode
2024-12-14 deleting old cube projects
2024-12-14 mac address
2024-12-15 strcasecmp in interface
2024-12-15 setting L2 current direction based on parameter DIR
2024-12-15 lema and seta calibration for tock driver
2024-12-15 comments
2024-12-15 setting gate based on table and fractional values - initially tested
2024-12-18 adding values to g_tab up to 25A
2025-01-02 adding calibration procedure - not tested yet
2025-01-02 cycle set to 200us, switching ld1 using registers (not HAL)
2025-01-02 switching directions coils using registers instead of hal
2025-01-02 changing conversions to 25 and cycle to 110us
2025-01-05 working on calibaration
2025-01-05 smoth current change using ermax
2025-01-05 readme
2025-01-21 working on g_tab if filled with zeros
2025-01-21 g_tab step changed from 1A to 0.1A
2025-02-14 bugfix: driver for 4th T, capacitors for input amps
2025-02-16 save g_tab in flash
2025-02-20 saving/loading parameters to flash
2025-05-19 adding mode 3, adding delay on start
2025-05-28 comments, cleaning, removing wrong pid_out limits
2025-05-28 code cleaning
2025-06-11 working on direction switching - just current limit
2025-06-11 switching direction using negative set_A
2025-07-25 readme update for aqura
2025-07-28 new static IP, readme
2025-07-29 no welcome message, set last mode after 0 current callibration
2025-08-07 g_tab extended from 30 to 100 A, mac changed
2025-10-07 python nc like script
2025-10-08 pnc, adding bat and timoout 0.05
2025-10-08 readme_aqura
2025-10-08 partial merge with test
2025-12-01 acknowledgements
2026-06-08 rescale input, ttl_on
